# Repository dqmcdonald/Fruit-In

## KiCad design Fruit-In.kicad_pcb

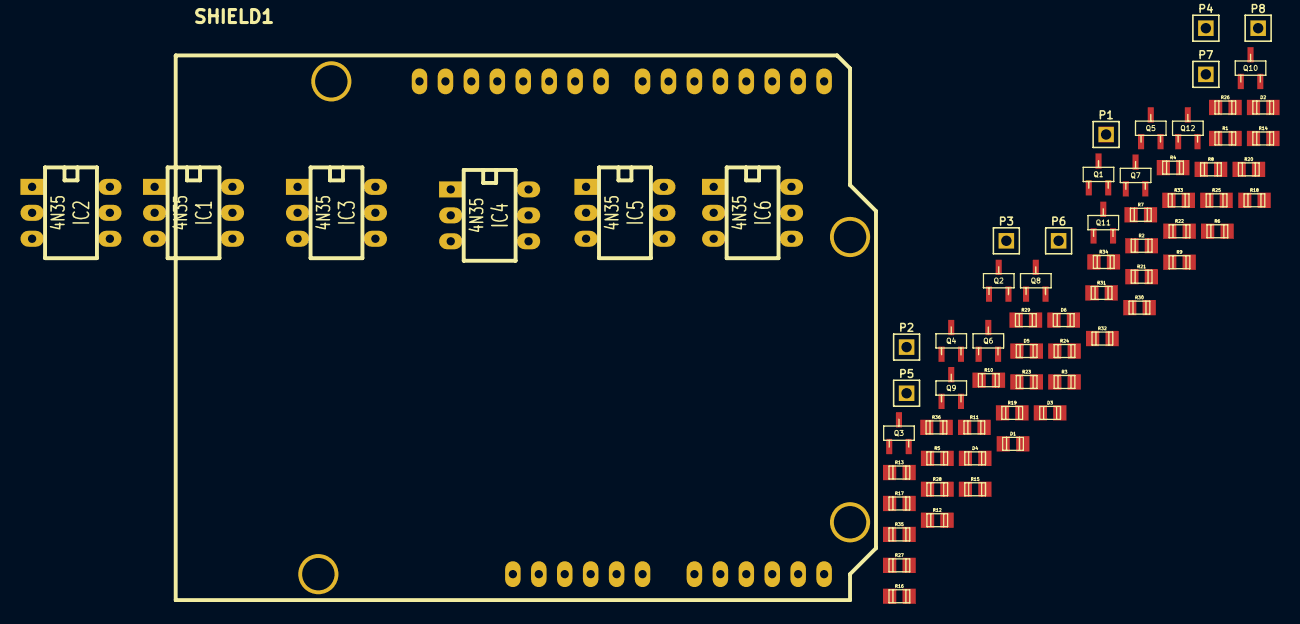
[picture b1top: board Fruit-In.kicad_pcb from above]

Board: 2 copper layers, 69 parts (0 on the bottom side), 50 nets, no tracks yet.

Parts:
D1, D2, D3, D4, D5, D6: LED; c_0805
IC1, IC2, IC3, IC4, IC5, IC6: 4N35; DIP-6__300_ELL
P1, P2, P3, P4, P5, P6, P7, P8: CONN_1; PIN_ARRAY_1
Q1, Q2, Q3, Q4, Q5, Q6, Q7, Q8, Q9, Q10, Q11, Q12: 2N3904; sot23
R1, R2, R3, R19, R25, R26: 2.2M; c_0805
R4, R5, R6, R13, R14, R15, R20, R23, R27, R28, R33, R34: 10K; c_0805
R7, R8, R9, R10, R11, R12, R21, R22, R29, R30, R31, R32: 220 Ohms; c_0805
R16, R17, R18, R24, R35, R36: 470 Ohms; c_0805
SHIELD1: ARDUINO_SHIELD

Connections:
+5V: R7.2, R8.2, R9.2, R10.2, R11.2, R12.2, R21.2, R22.2, R29.2, R30.2, R31.2, R32.2, SHIELD1.5V
D7: IC6.4, R34.1, R36.1, SHIELD1.7
D8: IC5.4, R33.1, R35.1, SHIELD1.8
D9: IC4.4, R23.1, R24.1, SHIELD1.9
D10: IC3.4, R15.1, R18.1, SHIELD1.10
D11: IC1.4, R13.1, R16.1, SHIELD1.11
D12: IC2.4, R14.1, R17.1, SHIELD1.12
GND: D1.2, D2.2, D3.2, D4.2, D5.2, D6.2, P7.1, P8.1, Q4.1, Q5.1, Q6.1, Q8.1, Q11.1, Q12.1, R1.2, R2.2, R3.2, R13.2, R14.2, R15.2, R19.2, R23.2, R25.2, R26.2, R33.2, R34.2, SHIELD1.GND2
unnamed: D1.1, R16.2
unnamed: D2.1, R17.2
unnamed: D3.1, R18.2
unnamed: D4.1, R24.2
unnamed: D5.1, R35.2
unnamed: D6.1, R36.2
unnamed: IC1.1, R7.1
unnamed: IC1.2, Q1.3, Q4.3
unnamed: IC1.5, R10.1
unnamed: IC2.1, R8.1
unnamed: IC2.2, Q2.3, Q5.3
unnamed: IC2.5, R11.1
unnamed: IC3.1, R9.1
unnamed: IC3.2, Q3.3, Q6.3
unnamed: IC3.5, R12.1
unnamed: IC4.1, R21.1
unnamed: IC4.2, Q7.3, Q8.3
unnamed: IC4.5, R22.1
unnamed: IC5.1, R29.1
unnamed: IC5.2, Q9.3, Q11.3
unnamed: IC5.5, R31.1
unnamed: IC6.1, R30.1
unnamed: IC6.2, Q10.3, Q12.3
unnamed: IC6.5, R32.1
unnamed: P1.1, R1.1, R4.2
unnamed: P2.1, R2.1, R5.2
unnamed: P3.1, R3.1, R6.2
unnamed: P4.1, R19.1, R20.2
unnamed: P5.1, R25.1, R27.2
unnamed: P6.1, R26.1, R28.2
unnamed: Q1.1, Q4.2
unnamed: Q1.2, R4.1
unnamed: Q2.1, Q5.2
unnamed: Q2.2, R5.1
unnamed: Q3.1, Q6.2
unnamed: Q3.2, R6.1
unnamed: Q7.1, Q8.2
unnamed: Q7.2, R20.1
unnamed: Q9.2, R27.1
unnamed: Q10.1, Q12.2
unnamed: Q10.2, R28.1
unnamed: Q9.1, Q11.2

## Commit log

2014-08-25 Fruit-In Shield
    Touch sensor shield
2014-08-26 Final version sent to OSH Park
2014-09-16 Small update
2014-09-16 Small layout changes
